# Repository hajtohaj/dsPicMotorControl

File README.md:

My first microchip project based on stuff found in the garage
Goal is to learn microchip programming for home use by implementing gradual
- blinking diode
- Read quadrature encoder signal from pololu 37D brushed DC motor; [probably this](https://www.pololu.com/product/4691)
- Drive motor with PWM using [Dual Serial Motor Controller](https://www.pololu.com/product/2078)
- Communicate over CAN with older [BeagleBone® Black](https://www.beagleboard.org/boards/beaglebone-black). CAN description on [Microchip Developer Help](https://developerhelp.microchip.com/xwiki/bin/view/applications/can/), [AN1249](https://ww1.microchip.com/downloads/aemDocuments/documents/OTH/ApplicationNotes/ApplicationNotes/01249A.pdf)
- PLC1602JHW-FWLW LCD Display [spec](https://www.openhacks.com/uploadsproductos/eone-1602a1.pdf) or [spec](https://www.micros.com.pl/mediaserver/O_LCM162-wfpc_0001.pdf) [spec](https://www.hantronix.com/down/ks0066u.pdf), more [info](https://www.gibbard.me/hd44780_lcd_screen/), and [more](https://www.analog.com/media/en/technical-documentation/application-notes/AN-908.pdf) and [more](https://www.alldatasheet.pl/datasheet-pdf/view/63663/HITACHI/HD44780U.html) and [more](https://www.pantechsolutions.net/how-to-interface-lcd-with-dspic30f4011-dspic-evaluation-board)

Microcontroller: dsPIC33FJ64MC802

Breadboard is used for setup

Programmer/Debugger: MPLAB ICD 3 (considering upgrade to PICkit™ 5: PG164150)

Readings: 
- dsPIC33FJ64MC802 [Datasheet](https://ww1.microchip.com/downloads/aemDocuments/documents/OTH/ProductDocuments/DataSheets/70291G.pdf)
- dsPIC33F/PIC24H Family Reference Manual, published as separate chapters, e.g.
  - [Section 7. Oscillator](https://ww1.microchip.com/downloads/en/DeviceDoc/70186E.pdf)
  - [Section 10. I/O Ports](https://ww1.microchip.com/downloads/aemDocuments/documents/OTH/ProductDocuments/ReferenceManuals/70193D.pdf)
  - [Quadrature Encoder Interface (QEI)](https://ww1.microchip.com/downloads/aemDocuments/documents/MCU16/ProductDocuments/ReferenceManuals/dsPIC33-PIC24-FRM-Quadrature-Encoder-Interface-QEI-DS70000601D.pdf)
- [dsPIC33A Programmer's Reference Manual](https://ww1.microchip.com/downloads/aemDocuments/documents/MCU16/ProductDocuments/ReferenceManuals/dsPIC33A-Programmers-Reference-Manual-DS70005540.pdf)
- [MPLAB XC-DSC C Compiler User's Guide](https://ww1.microchip.com/downloads/aemDocuments/documents/DEV/ProductDocuments/UserGuides/MPLAB-XC-DSC-C-Compiler-User-Guide-DS50003589.pdf)
- [MPLAB XC-DSC Libraries Reference Manual](https://ww1.microchip.com/downloads/aemDocuments/documents/DEV/ProductDocuments/ReferenceManuals/MPLAB-XC-DSC-Libraries-Reference-Manual-DS50003591.pdf)
- [MPLAB XC-DSC Assembler, Linker and Utilities User's Guide](https://ww1.microchip.com/downloads/aemDocuments/documents/DEV/ProductDocuments/UserGuides/MPLAB-XC-DSC-Assembler-Linker-and-Utilities-User-Guide-DS50003590.pdf)
- [Developer Help](https://developerhelp.microchip.com/xwiki/bin/view/Main/)

Video:
 - [Create! - 01 Setting up the PIC Microcontroller (Quick and Easy)](https://www.youtube.com/watch?v=CSCDfCr5kDo&t=996s)

Notes:
- To push to github from MPLAB X "you must create a personal access token to use as a password when authenticating to GitHub" [ref](https://microchip.my.site.com/s/article/Github-2-factor-authentification-in-MPLAB-X)
- Order PCB on https://www.pcbway.com (Using KiCad plugin)

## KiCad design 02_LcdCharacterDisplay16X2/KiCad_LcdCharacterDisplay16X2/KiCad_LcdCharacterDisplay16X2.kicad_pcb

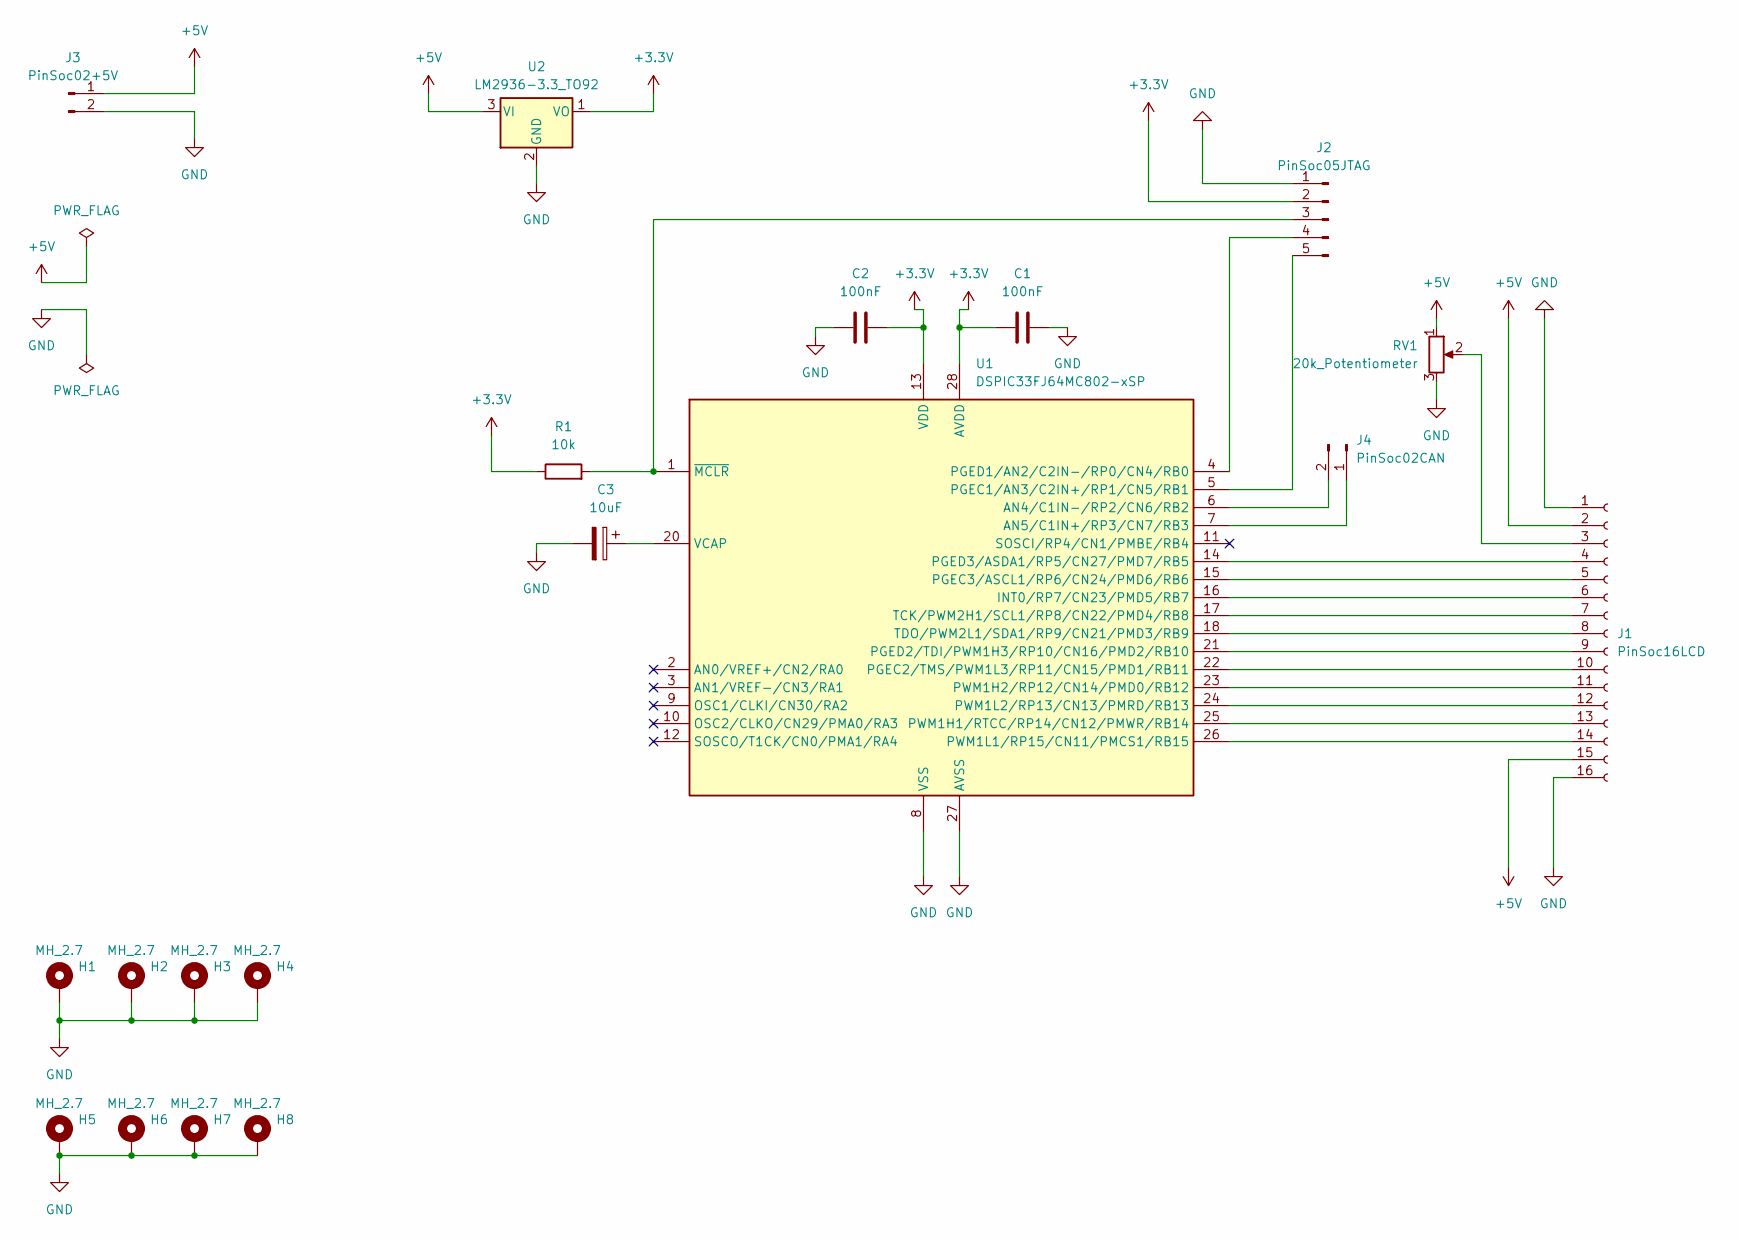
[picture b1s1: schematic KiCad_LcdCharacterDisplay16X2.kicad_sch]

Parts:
C1, C2: 100nF; CP_Radial_Tantal_D5.0mm_P5.00mm
C3: 10uF; CP_Radial_Tantal_D5.0mm_P5.00mm
H1, H2, H3, H4, H5, H6, H7, H8: MH_2.7; MountingHole_2.7mm_M2.5_ISO7380_Pad
J1: PinSoc16LCD; PinSocket_1x16_P2.54mm_Vertical
J2: PinSoc05JTAG; PinSocket_1x05_P2.54mm_Vertical
J3: PinSoc02+5V; PinSocket_1x02_P2.54mm_Vertical
J4: PinSoc02CAN; PinSocket_1x02_P2.54mm_Vertical
R1: 10k; R_Axial_DIN0207_L6.3mm_D2.5mm_P15.24mm_Horizontal
RV1: 20k_Potentiometer; Potentiometer_Bourns_3386P_Vertical
U1: DSPIC33FJ64MC802-xSP; DIP-28_W7.62mm
U2: LM2936-3.3_TO92; TO-92_Inline

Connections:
+3.3V: C1.1, C2.1, J2.2, R1.1, U1.13 (VDD), U1.28 (AVDD), U2.1 (VO)
+5V: J1.2, J1.15, J3.1, RV1.1, U2.3 (VI)
GND: C1.2, C2.2, C3.2, H1.1, H2.1, H3.1, H4.1, H5.1, H6.1, H7.1, H8.1, J1.1, J1.16, J2.1, J3.2, RV1.3, U1.8 (VSS), U1.19 (VSS), U1.27 (AVSS), U2.2 (GND)
unnamed: J1.3, RV1.2
unnamed: J1.4, U1.14 (PGED3/ASDA1/RP5/CN27/PMD7/RB5)
unnamed: J1.5, U1.15 (PGEC3/ASCL1/RP6/CN24/PMD6/RB6)
unnamed: J1.6, U1.16 (INT0/RP7/CN23/PMD5/RB7)
unnamed: J1.7, U1.17 (TCK/PWM2H1/SCL1/RP8/CN22/PMD4/RB8)
unnamed: J1.8, U1.18 (TDO/PWM2L1/SDA1/RP9/CN21/PMD3/RB9)
unnamed: J1.9, U1.21 (PGED2/TDI/PWM1H3/RP10/CN16/PMD2/RB10)
unnamed: J1.10, U1.22 (PGEC2/TMS/PWM1L3/RP11/CN15/PMD1/RB11)
unnamed: J1.11, U1.23 (PWM1H2/RP12/CN14/PMD0/RB12)
unnamed: J1.12, U1.24 (PWM1L2/RP13/CN13/PMRD/RB13)
unnamed: J1.13, U1.25 (PWM1H1/RTCC/RP14/CN12/PMWR/RB14)
unnamed: J1.14, U1.26 (PWM1L1/RP15/CN11/PMCS1/RB15)
unnamed: J2.3, R1.2, U1.1 (~MCLR)
unnamed: J2.4, U1.4 (PGED1/AN2/C2IN-/RP0/CN4/RB0)
unnamed: J2.5, U1.5 (PGEC1/AN3/C2IN+/RP1/CN5/RB1)
unnamed: J4.1, U1.7 (AN5/C1IN+/RP3/CN7/RB3)
unnamed: J4.2, U1.6 (AN4/C1IN-/RP2/CN6/RB2)
unnamed: C3.1, U1.20 (VCAP)

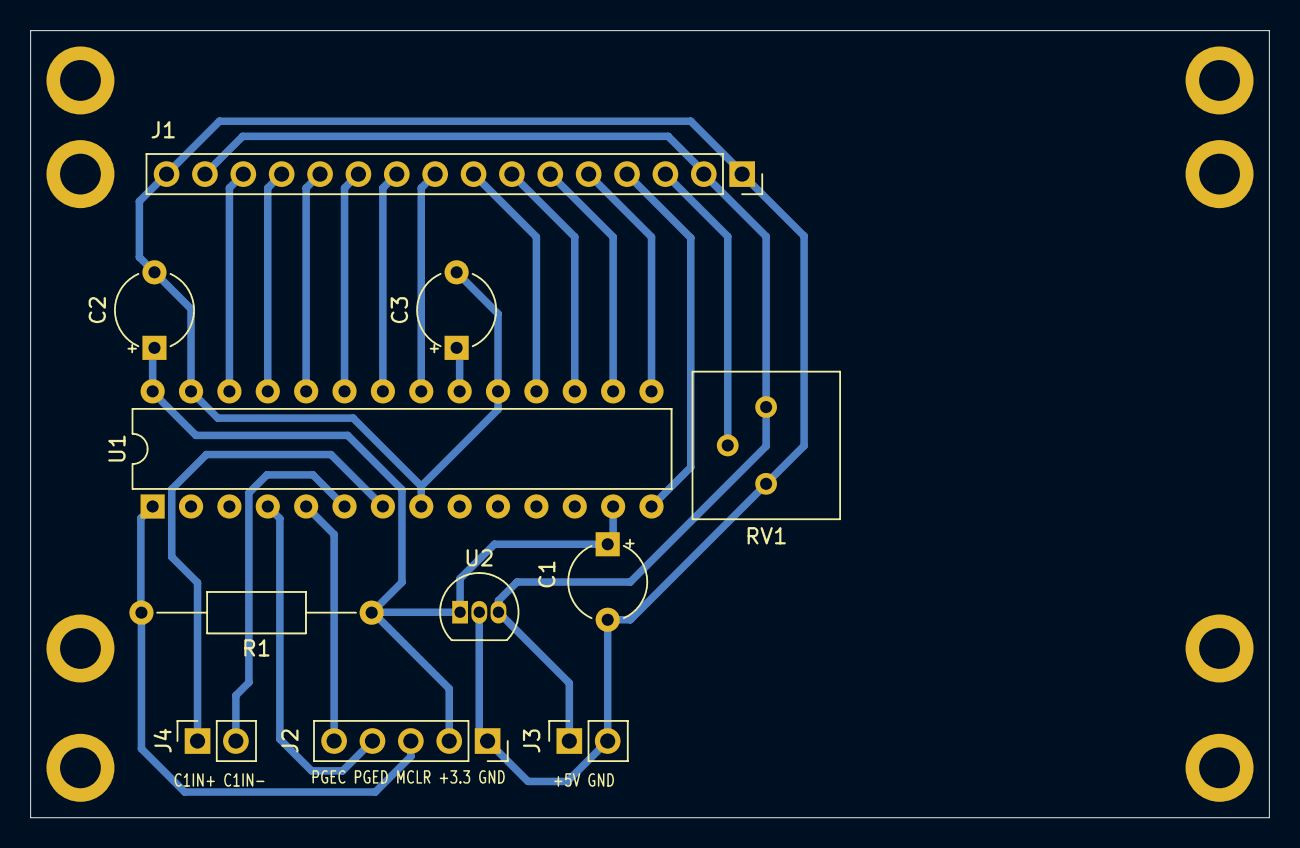
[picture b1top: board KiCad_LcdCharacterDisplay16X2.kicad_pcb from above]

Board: 2 copper layers, 82.0 x 52.1 mm, 19 parts (0 on the bottom side), 21 nets.

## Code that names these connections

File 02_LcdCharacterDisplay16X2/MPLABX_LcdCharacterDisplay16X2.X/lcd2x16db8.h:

/* 
 * File:   lcd2x16db8.h
 * Author: tomas
 *
 * Created on 22 grudnia 2024, 12:58
 */

#ifndef LCD2X16DB8_H
#define	LCD2X16DB8_H

#ifdef	__cplusplus
extern "C" {
#endif
#include <xc.h>

#ifndef FCY
#define FCY 3574000UL  // Fosc(FRC)= 7.37Mhz(7370000Hz) -> Fcy = Fosc/2 = 3685000
#include <libpic30.h>   //to use __delay_us, FCY must be defined before include
#endif
    
// LCD Itf Signals (register initialization in init_lcd_itf()
#define LCD_RSPin LATBbits.LATB5        // RB5 (LCD RS, Pin4)Register Select H:Data Input L:Instruction Input
#define LCD_RS_INSTRUCTION  0           // LCD Instruction register 
#define LCD_RS_DATA  1                  // LCD Data register
#define LCD_RWPin LATBbits.LATB6        // RB6 (LCD R/W Pin 5) R/W select H:Read, L:Write  
#define LCD_RW_WRITE  0                 // 
#define LCD_RW_READ  1                  // LCD Data register
#define LCD_EPin  LATBbits.LATB7        // RB7 (LCD E Pin 6)Enable Signal
#define LCD_E_HIGH 1                    //
#define LCD_E_LOW 0                     //
#define LCD_E_PULSE_WIDTH_US 0x0001     //
#define LCD_BFBit PORTBbits.RB15        //
#define LCD_DB_TRIS  TRISB              //
#define LCD_DB_TRIS_INPUT 0xFF00        //
#define LCD_DB_TRIS_OUTPUT 0x001F       // 
#define LCD_DB_LAT  LATB                //               
#define LCD_DB_PORT  PORTB              //
#define LCD_DB_SET_PORT_PINS  0xFF00    //
#define LCD_DB_CLEAR_PORT_PINS  0x00FF  // 
#define LCD_DISPLAY_ON   0x0004         //
#define LCD_DISPLAY_OFF  0x0000         //            
#define LCD_CURSOR_ON  0x0002           //                  
#define LCD_CURSOR_OFF  0x0000          //
#define LCD_CURSOR_BLINK_ON  0x0001     //                  
#define LCD_CURSOR_BLINK_OFF  0x0000    //
#define LCD_FIRST_LINE_START 0x0000     //
#define LCD_SECOND_LINE_START 0x0040    //
#define LCD_LINE_LENGTH 24              //
#define LCD_LINE_LENGTH_VISIBLE 16      //

void lcd_db8_init(void);
void lcd_db8_print_character(char);
void lcd_db8_print_string(char*);
void lcd_db8_go_home(void);
void lcd_db8_go_line1_home(void);
void lcd_db8_go_line2_home(void);
void lcd_db8_go_to_position(unsigned char);
void lcd_db8_clear_screen(void);
void lcd_db8_clear_line1(void);
void lcd_db8_clear_line2(void);
void lcd_db8_set_display_set_cursor(unsigned char, unsigned char, unsigned char);

#ifdef	__cplusplus
}
#endif

#endif	/* LCD2X16DB8_H */

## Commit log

2024-11-30 First commit from MPLAB X
2024-12-01 Update README.md
    Adding link to FRM Quadrature Encoder Interface (QEI)
2024-12-02 Update README.md
    Adding link to LCD Display Spec
2024-12-02 Blinking diode
2024-12-02 try again
2024-12-02 Remove ignored files
2024-12-02 Update README.md
    Add link to example of LCD Display implementation
2024-12-08 Update README.md
    Update link to Programers reference manual. Previous pointed to a wrong chip family
2024-12-08 initializing repo
2024-12-08 Update README.md
    Add Link to CAN description
2024-12-08 Update README.md
    Adding link to PCBWay - PCB manufacturing company
2024-12-14 Update README.md
    More spec about LCD
2024-12-15 Update README.md
    More LCD info
2024-12-22 Lcd display library
2024-12-22 Update README.md
    add link to can an1249
2025-05-03 uart
